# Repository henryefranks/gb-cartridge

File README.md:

# Game Boy Cartridge and Programmer

This repo contains schematics and code for a programmable Game Boy cartridge and
associated programmer. The Cartridge utilises an AT28C256-15PU 32k EEPROM, so
ROM size is limited to 32kB. I have designed the programmer around an Arduino
Nano, although it may be possible to use other models.

---

### Uploading the ROM to the Cartridge

To upload the ROM, use
`python3 programmer/send_rom.py -p path/to/rom.gb -s /path/to/serial/port`

This sends the ROM to the Arduino to load onto the EEPROM, using the *Janky
Communications Protocol* (JCP), a highly custom, highly nonstandard handshake
system I created. This is far from best practice, but it gets the job done...

### How JCP Works

NB: In all serial 'exchanges' shown below, *[programmer]* denotes the Arduino,
and *[controller]* denotes the host computing sending the ROM.

JCP first establishes a connection between the two devices using Syn/Ack. The
exchange is as follows:

```
[programmer]: SYN
[controller]: SYNACK
[programmer]: ACK
```

Connection is now established, and ROM data can be sent to the programmer. Each
byte of ROM data sent follows a similar handshake process to avoid problems with
serial buffer overflow and timing. The exchange is as follows:

```
[programmer]: SEND
[controller]: XX
[programmer]: LOAD <XXXX: XX>
```

The data shown in the exchange above is denoted by (X) placeholders, and in
reality is any combination of hexadecimal data. The data denoted *XX* represents
a single byte of data, which is the data sent by the controller in the first
case, and the data received by the programmer in the second. This data should be
checked for parity in order to ensure data received by the programmer (and hence
sent to the EEPROM) matches what was intended. The data denoted *XXXX* is the
address the data is written to, and again should be checked against the intended
value. send_rom.py handles this validation and will show a serial traceback if
there is a mismatch.

For example, if the controller wanted to send the data `0B F3 54 2C`, that
would look like:

```
[programmer]: SYN
[controller]: SYNACK
[programmer]: ACK
[programmer]: SEND
[controller]: 0B
[programmer]: LOAD <0000: 0B>
[programmer]: SEND
[controller]: F3
[programmer]: LOAD <0001: F3>
[programmer]: SEND
[controller]: 54
[programmer]: LOAD <0001: 54>
[programmer]: SEND
[controller]: 2C
[programmer]: LOAD <0003: 2C>
```
There are currently known bugs with this process, some of which are covered in
the 'future developments' section of this document.

---

### Reading the schematics
Schematics are drawn in KiCAD 5, and all additional footprints are included in
the `lib` folder.

---

### Future Developments
- send_rom.py currently does not stop at 7FFF
- add connection termination feature from controller -> programmer
- speed up JCP
- Use custom ATMega or other MCU setup instead of Arduino in programmer

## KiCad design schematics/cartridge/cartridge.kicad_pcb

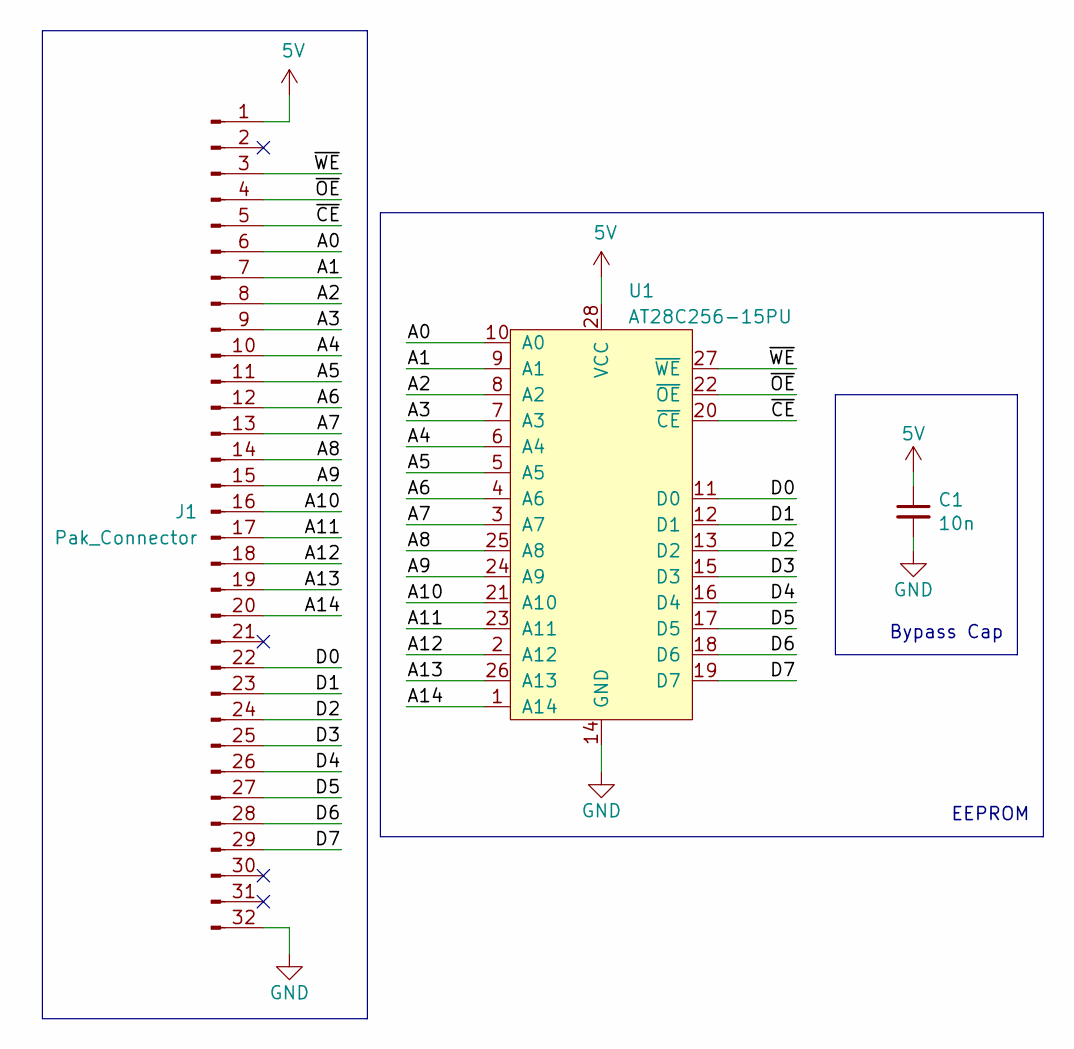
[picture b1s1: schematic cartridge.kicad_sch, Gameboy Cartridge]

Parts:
C1: 10n; C_0805
J1: Pak_Connector
U1: AT28C256-15PU; DIP_Socket_28

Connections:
5V: C1.1, J1.1, U1.28 (VCC)
/A0: J1.6, U1.10 (A0)
/A1: J1.7, U1.9 (A1)
/A2: J1.8, U1.8 (A2)
/A3: J1.9, U1.7 (A3)
/A4: J1.10, U1.6 (A4)
/A5: J1.11, U1.5 (A5)
/A6: J1.12, U1.4 (A6)
/A7: J1.13, U1.3 (A7)
/A8: J1.14, U1.25 (A8)
/A9: J1.15, U1.24 (A9)
/A10: J1.16, U1.21 (A10)
/A11: J1.17, U1.23 (A11)
/A12: J1.18, U1.2 (A12)
/A13: J1.19, U1.26 (A13)
/A14: J1.20, U1.1 (A14)
/D0: J1.22, U1.11 (D0)
/D1: J1.23, U1.12 (D1)
/D2: J1.24, U1.13 (D2)
/D3: J1.25, U1.15 (D3)
/D4: J1.26, U1.16 (D4)
/D5: J1.27, U1.17 (D5)
/D6: J1.28, U1.18 (D6)
/D7: J1.29, U1.19 (D7)
/~CE: J1.5, U1.20 (~CE)
/~OE: J1.4, U1.22 (~OE)
/~WE: J1.3, U1.27 (~WE)
GND: C1.2, J1.32, U1.14 (GND)

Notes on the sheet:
EEPROM
Bypass Cap

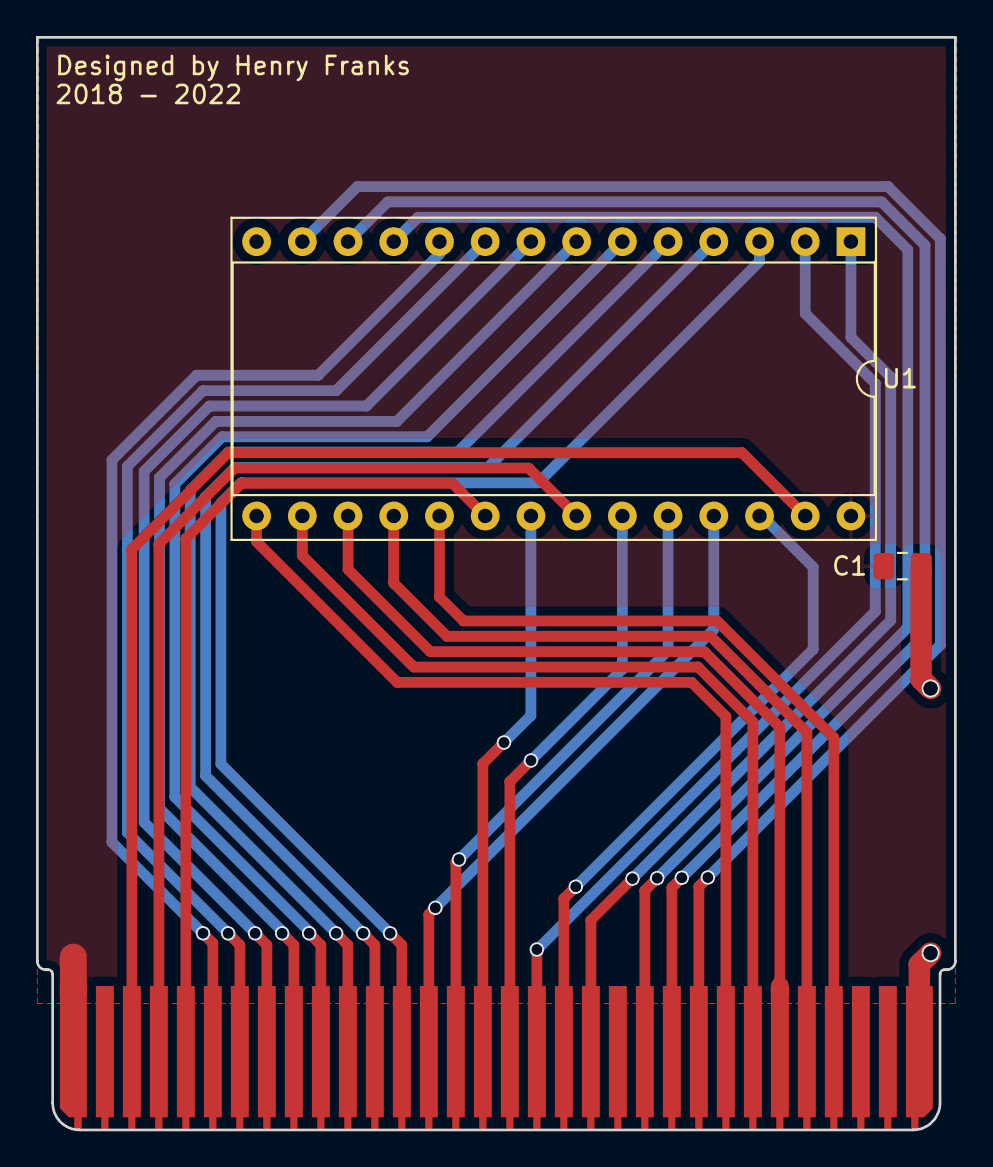
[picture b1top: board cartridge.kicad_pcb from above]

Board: 2 copper layers, 51.0 x 60.7 mm, 3 parts (0 on the bottom side), 28 nets.

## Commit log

2019-12-18 Removed hidden files
2020-05-28 Add AT28C256 library
2020-05-28 Update schematic to use new lib
2020-05-29 Add gitignore
2020-05-29 Restructure and add programmer
2020-05-29 Change line endings to LF
2020-05-29 More line ending conversion
2020-05-29 Add README
2020-05-30 Add argument parser description
2021-02-14 Add pong ROM
2021-02-20 Windows compatibility
2021-02-20 Reorganise folders and split some subroutines into separate files
2021-02-20 Update gitignore
2021-02-20 Further reorganisation (and unify indentation to spaces)
2021-03-02 Add global makefile and remove old make components from pong
2021-03-02 Restructure pong to work with new makefile
2021-03-02 Create simple sound demo ROM
2021-10-15 Tweak sound ROM beeps
2021-10-15 Update symbol library position
2021-10-15 Enable channel 3 playback
2021-10-16 Play C major on CH3
2021-10-16 Minor optimisations
2021-10-16 Use sine for CH3
2021-10-17 Update sound README
2021-10-17 Ignore .gb files
2021-12-31 New board layout
2022-01-26 Slightly edit silkscreen text for manufacture
2022-06-30 New ROM loader firmware
2022-12-11 Remove ROMs in favour of separate repo
